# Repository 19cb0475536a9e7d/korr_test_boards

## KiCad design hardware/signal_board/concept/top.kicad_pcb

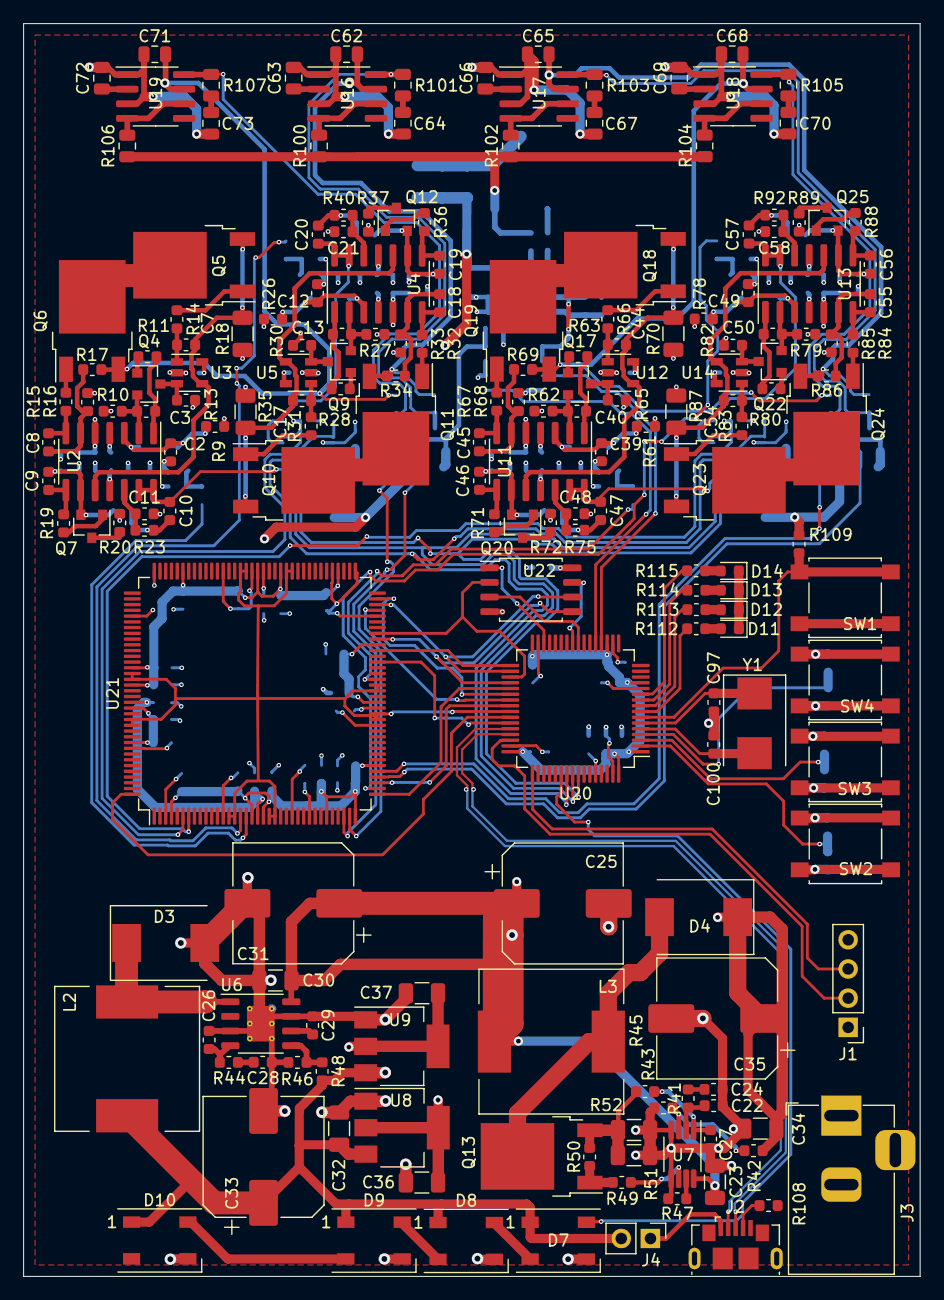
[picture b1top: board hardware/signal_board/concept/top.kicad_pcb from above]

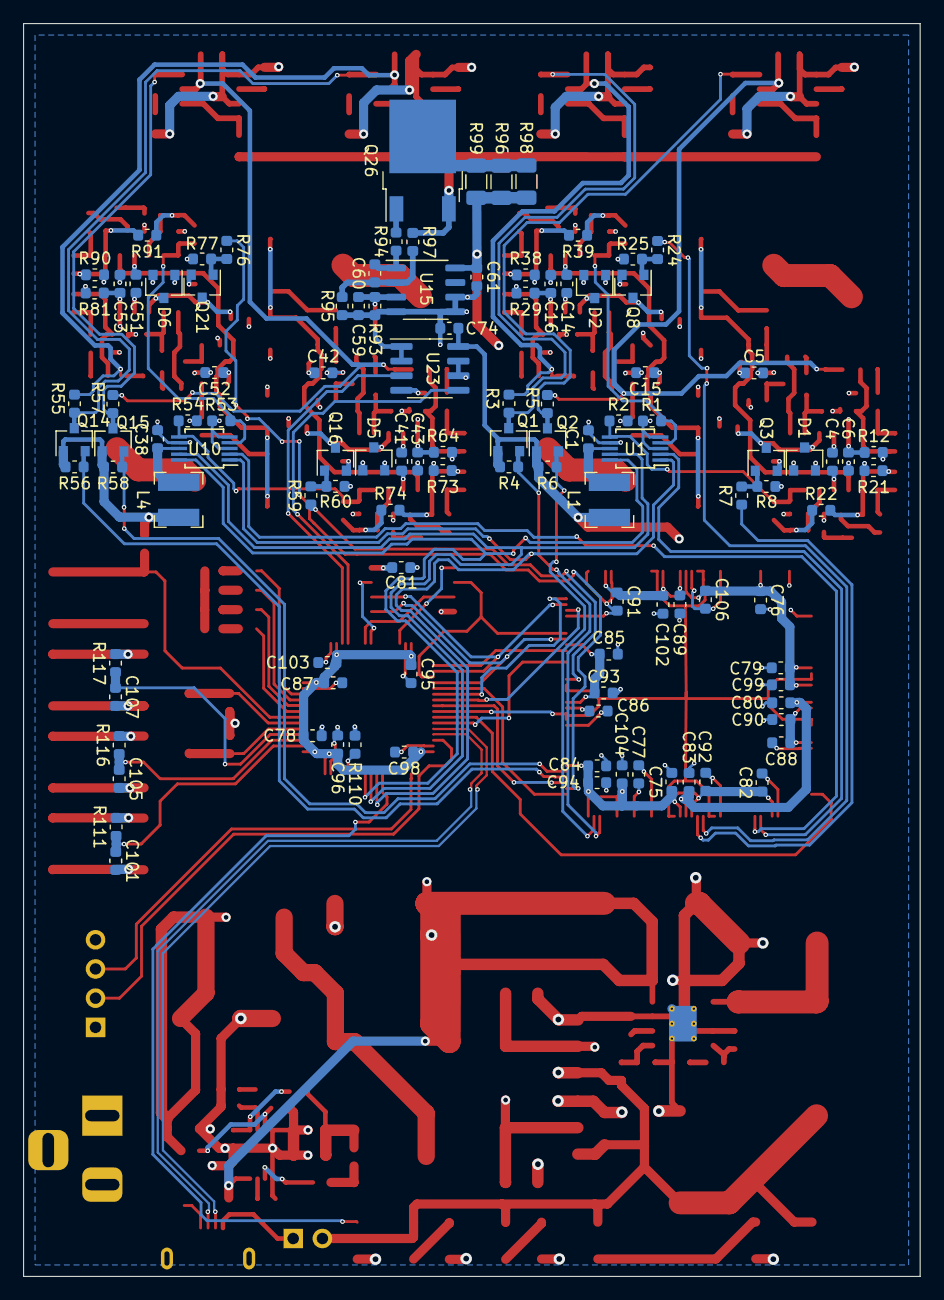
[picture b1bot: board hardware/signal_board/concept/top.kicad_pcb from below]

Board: 4 copper layers, 78.0 x 109.0 mm, 300 parts (111 on the bottom side), 186 nets.

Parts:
C1, C2, C4, C5, C6, C11, C12, C14, C15, C16, C21, C24, C27, C28, C29, C38, C39, C41, C42, C43, C48, C49, C51, C52, C53, C58, C59, C61, C74, C75, C76, C77, C78, C79, C80, C81, C82, C83, C84, C85, C86, C87, C88, C89, C90, C91, C92, C93, C94, C95, C96, C98, C99, C101, C102, C103, C104, C105, C106, C107: 0.1u; C_0603_1608Metric
C3, C7, C8, C9, C13, C17, C18, C19, C22, C26, C40, C44, C45, C46, C50, C54, C55, C56, C60: 100p; C_0603_1608Metric
C10, C20, C47, C57: 0.22u; C_0603_1608Metric
C23, C30, C32, C34, C36, C37: 1u; C_1206_3216Metric
C25, C31: 470u; CP_Elec_10x10
C33, C35: 100u; CP_Elec_10x10
C62, C65, C68, C71: 0.1u; C_0805_2012Metric
C63, C66, C69, C72: 470p; C_0805_2012Metric
C64, C67, C70, C73: 1u; C_0805_2012Metric
C97, C100: 10p; C_0603_1608Metric
D1, D2, D5, D6: BZX84Cxx; D_SOT-23_ANK
D3, D4: D_Schottky; D_SMC
D7, D8, D9, D10: WS2812B; LED_WS2812B_PLCC4_5.0x5.0mm_P3.2mm
D11, D12, D13, D14: LED; LED_0603_1608Metric
J1: Conn_01x04; PinHeader_1x04_P2.54mm_Vertical
J2: USB_OTG; USB_Micro-B_GCT_USB3076-30-A
J3: Barrel_Jack_Switch; BarrelJack_Horizontal
J4: Conn_01x02; PinHeader_1x02_P2.54mm_Vertical
L1, L4: 10u; L_Bourns-SRN4018
L2, L3: 10u; L_12x12mm_H8mm
Q1, Q2, Q3, Q4, Q7, Q8, Q9, Q12, Q14, Q15, Q16, Q17, Q20, Q21, Q22, Q25: Q_NMOS_GSD; SOT-23
Q5, Q10, Q18, Q23: Q_PMOS_GDS; TO-252-2
Q6, Q11, Q13, Q19, Q24, Q26: Q_NMOS_GDS; TO-252-2
R1, R2, R3, R4, R5, R6, R8, R9, R10, R13, R20, R21, R25, R26, R27, R30, R37, R38, R53, R54, R55, R56, R57, R58, R60, R61, R62, R65, R72, R73, R77, R78, R79, R82, R89, R90, R109, R110: 10k; R_0603_1608Metric
R7, R24, R59, R76: 100; R_0603_1608Metric
R11, R14, R15, R16, R19, R22, R23, R28, R31, R32, R33, R36, R39, R40, R41, R44, R63, R66, R67, R68, R71, R74, R75, R80, R83, R84, R85, R88, R91, R92, R94, R95, R97, R108, R111, R112, R113, R114, R115, R116, R117: 1k; R_0603_1608Metric
R12, R29, R64, R81, R93: 100k; R_0603_1608Metric
R17, R34, R69, R86: 9.1k; R_0603_1608Metric
R18, R35, R70, R87: 1k; R_1206_3216Metric
R42, R43, R45, R46, R47, R48, R50: 10K; R_0603_1608Metric
R49: 22; R_0603_1608Metric
R51, R52: 0.1; R_1206_3216Metric
R96, R98, R99: 100; R_1206_3216Metric
R100, R102, R104, R106: 470; R_0805_2012Metric
R101, R103, R105, R107: 10k; R_0805_2012Metric
SW1, SW2, SW3, SW4: SW_Push; SW_SPST_B3S-1000
U1, U10: ADS1118IDGS; MSOP-10_3x3mm_P0.5mm
U2, U4, U11, U13: LM324; SOIC-14_3.9x8.7mm_P1.27mm
U3, U5, U12, U14: MCP6001-OT; SOT-23-5
U6: L5973D; HSOP-8-1EP_3.9x4.9mm_P1.27mm_EP2.41x3.1mm_ThermalVias
U7: LM3488MM; MSOP-8_3x3mm_P0.65mm
U8: AMS1117-3.3; SOT-223-3_TabPin2
U9: AMS1117; SOT-223-3_TabPin2
U15: LM358; SO-8_3.9x4.9mm_P1.27mm
U16, U17, U18, U19: IR1155S; SOIC-8_3.9x4.9mm_P1.27mm
U20: STM32F103R(F-G)Tx_u; LQFP-64_10x10mm_P0.5mm
U21: XC6SLX9-TQG144; TQFP-144_20x20mm_P0.5mm
U22: W25Q32JVSS; SOIC-8_5.23x5.23mm_P1.27mm
U23: MCP6002-xMS; SOIC-8_3.9x4.9mm_P1.27mm
Y1: 8MHz; Crystal_SMD_7050-2Pin_7.0x5.0mm

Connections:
/ADS1118_MISO: U1.9, U10.9, U20.56
/ADS1118_MOSI: U1.10, U10.10, U20.57
/ADS1118_NCS_0: U1.2, U21.6
/ADS1118_NCS_1: U10.2, U21.7
/ADS1118_SCK: U1.1, U10.1, U20.55
/Cell_0_Sheet/CurrentSource_A_Sheet/PFC_CRNT: C20.1, R1.1, U1.4, U4.13, U4.14
/Cell_0_Sheet/CurrentSource_B_Sheet/PFC_CRNT: C10.1, R2.1, U1.6, U2.13, U2.14
/Cell_1_Sheet/CurrentSource_A_Sheet/PFC_CRNT: C57.1, R53.1, U10.4, U13.13, U13.14
/Cell_1_Sheet/CurrentSource_B_Sheet/PFC_CRNT: C47.1, R54.1, U10.6, U11.13, U11.14
/CoreSheet/STM32F103_BTN_0: C101.1, R111.1, U20.2
/CoreSheet/STM32F103_BTN_1: C105.1, R116.1, U20.3
/CoreSheet/STM32F103_BTN_2: C107.1, R117.1, U20.4
/CoreSheet/STM32F103_SIG_LED_0: R112.1, U20.8
/CoreSheet/STM32F103_SIG_LED_1: R113.1, U20.9
/CoreSheet/STM32F103_SIG_LED_2: R114.1, U20.10
/CoreSheet/STM32F103_SIG_LED_3: R115.1, U20.11
/CoreSheet/U_PFC_FB_OVP_ADJ_DAC: U20.20, U23.3
/CoreSheet/U_PFC_VCC_ADJ_DAC: U20.21, U23.5
/CoreSheet/W25Q32_HOLD: U20.25, U22.7
/CoreSheet/W25Q32_NCS: U20.30, U22.1
/CoreSheet/W25Q32_NWP: U20.24, U22.3
/CoreSheet/XC6SLX9_CLK: U20.41, U21.14, U21.15, U21.21, U21.22, U21.50, U21.51, U21.55, U21.56, U21.84, U21.85, U21.92, U21.93, U21.123, U21.124, U21.131, U21.132
/CoreSheet/XC6SLX9_DONE: U20.38, U21.71
/CoreSheet/XC6SLX9_HSWAPEN: U20.42, U21.144
/CoreSheet/XC6SLX9_INIT_B: U20.40, U21.39
/CoreSheet/XC6SLX9_M0: U20.39, U21.69
/CoreSheet/XC6SLX9_M1: U20.43, U21.60
/CoreSheet/XC6SLX9_NCS: U20.33, U21.62
/CoreSheet/XC6SLX9_PRG_B: U20.37, U21.37
/CoreSheet/XC6SLX9_W25Q32_MISO: U20.35, U21.65, U22.2
/CoreSheet/XC6SLX9_W25Q32_MOSI: U20.36, U21.64, U22.5
/CoreSheet/XC6SLX9_W25Q32_SCK: U20.34, U21.70, U22.6
/PFC_DUT_FB_OVP: Q26.3, R97.1, R100.1, R102.1, R104.1, R106.1
/PFC_GATE_HIGH_0: Q1.3, R3.1, R101.1, U16.8
/PFC_GATE_HIGH_1: Q2.3, R5.1, R107.1, U19.8
/PFC_GATE_HIGH_2: Q14.3, R55.1, R103.1, U17.8
/PFC_GATE_HIGH_3: Q15.3, R57.1, R105.1, U18.8
/PFC_GATE_LOW_0: Q1.2, R4.1, U21.34
/PFC_GATE_LOW_1: Q2.2, R6.1, U21.35
/PFC_GATE_LOW_2: Q14.2, R56.1, U21.40
/PFC_GATE_LOW_3: Q15.2, R58.1, U21.41
/PFC_STOP_0: R24.1, U21.16
/PFC_STOP_1: R7.1, U21.17
/PFC_STOP_2: R76.1, U21.38
/PFC_STOP_3: R59.1, U21.57
/PFC_VCC_DUT_0: C62.1, Q11.3, R3.2, R34.1, U16.7
/PFC_VCC_DUT_1: C71.1, Q6.3, R5.2, R17.1, U19.7
/PFC_VCC_DUT_2: C65.1, Q24.3, R55.2, R86.1, U17.7
/PFC_VCC_DUT_3: C68.1, Q19.3, R57.2, R69.1, U18.7
/STM32F103_SWCLK: J1.2, U20.46
/STM32F103_SWDIO: J1.3, U20.49
/STM32F103_USB_D+: J2.3, U20.45
/STM32F103_USB_D-: J2.2, U20.44
/U_PFC_FB_OVP_ADJ: C59.1, R93.1, U15.3, U23.1, U23.2
/U_PFC_VCC_ADJ: C6.1, C16.1, C43.1, C53.1, R12.1, R29.1, R64.1, R81.1, U2.5, U4.5, U11.5, U13.5, U23.6, U23.7
/VCC5V: C5.1, C15.1, C32.1, C33.1, C42.1, C52.1, D7.1, D8.1, D9.1, D10.1, J4.2, L2.2, R9.2, R26.2, R48.2, R61.2, R78.2, U3.5, U5.5, U8.3, U9.3, U12.5, U14.5
/VCC12V: C23.1, C25.1, C30.1, C31.1, C61.1, J3.1, L3.1, R96.1, R98.1, R99.1, U6.8, U7.8, U15.8
/VCC30V: C4.1, C14.1, C34.1, C35.1, C41.1, C51.1, D4.1, R13.1, R18.1, R20.1, R30.1, R35.1, R37.1, R42.2, R65.1, R70.1, R72.1, R82.1, R87.1, R89.1, U2.4, U4.4, U11.4, U13.4
/VDD1.25V: C37.2, C77.1, C80.1, C83.1, C86.1, C89.1, U9.2, U21.19, U21.28, U21.52, U21.89, U21.128
/VDD3.3V: C36.1, C74.1, C75.1, C76.1, C78.1, C79.1, C81.1, C82.1, C84.1, C85.1, C87.1, C88.1, C90.1, C91.1, C92.1, C93.1, C94.1, C95.1, C96.1, C98.1, C99.1, C102.1, C103.1, C104.1, C106.1, J1.4, L1.2, L4.2, Q1.1, Q2.1, Q14.1, Q15.1, R4.2, R6.2, R56.2, R58.2, R109.1, U8.2, U20.1, U20.13, U20.19, U20.32, U20.48, U20.64, U21.4, U21.18, U21.20, U21.31, U21.36, U21.42, U21.53, U21.63, U21.76, U21.86, U21.90, U21.103, U21.122, U21.125, U21.129, U21.135, U22.8, U23.8
/WS2812B_DIN: D7.4, U20.54
GNDA: C1.2, C2.2, C4.2, C5.2, C6.2, C11.2, C12.2, C14.2, C15.2, C16.2, C21.2, C22.2, C23.2, C24.2, C25.2, C26.2, C27.2, C28.2, C29.2, C30.2, C31.2, C32.2, C33.2, C34.2, C35.2, C36.2, C37.1, C38.2, C39.2, C41.2, C42.2, C43.2, C48.2, C49.2, C51.2, C52.2, C53.2, C58.2, C59.2, C61.2, C62.2, C63.2, C64.2, C65.2, C66.2, C67.2, C68.2, C69.2, C70.2, C71.2, C72.2, C73.2, C74.2, C75.2, C76.2, C77.2, C78.2, C79.2, C80.2, C81.2, C82.2, C83.2, C84.2, C85.2, C86.2, C87.2, C88.2, C89.2, C90.2, C91.2, C92.2, C93.2, C94.2, C95.2, C96.2, C97.2, C98.2, C99.2, C100.2, C101.2, C102.2, C103.2, C104.2, C105.2, C106.2, C107.2, D1.2, D2.2, D3.2, D5.2, D6.2, D7.3, D8.3, D9.3, D10.3, D11.1, D12.1, D13.1, D14.1, J1.1, J2.5, J2.6, J3.2, J3.3, Q3.2, Q8.2, Q16.2, Q21.2, R1.2, R2.2, R8.2, R10.2, R12.2, R16.2, R21.2, R25.2, R27.2, R29.2, R33.2, R38.2, R43.1, R46.1, R47.1, R51.1, R52.1, R53.2, R54.2, R60.2, R62.2, R64.2, R68.2, R73.2, R77.2, R79.2, R81.2, R85.2, R90.2, R93.2, R95.2, R108.2, R110.2, SW1.2, SW2.2, SW3.2, SW4.2, U1.3, U1.5, U1.7, U2.11, U3.2, U4.11, U5.2, U6.3, U6.7, U6.9, U7.4, U7.5, U8.1, U9.1, U10.3, U10.5, U10.7, U11.11, U12.2, U13.11, U14.2, U15.4, U15.5, U15.6, U16.1, U16.3, U17.1, U17.3, U18.1, U18.3, U19.1, U19.3, U20.12, U20.18, U20.31, U20.47, U20.63, U21.3, U21.13, U21.25, U21.49, U21.54, U21.68, U21.73, U21.77, U21.91, U21.96, U21.108, U21.113, U21.130, U21.136, U22.4, U23.4
unnamed: C1.1, L1.1, U1.8
unnamed: C2.1, D1.1, Q3.3, R9.1, U2.3
unnamed: C3.1, R11.2, U2.1
unnamed: C3.2, Q4.2, R10.1, U2.2
unnamed: C7.1, R14.2, U3.1
unnamed: C7.2, Q5.3, R18.2, U2.10, U3.4
unnamed: C8.1, R15.2, U2.7
unnamed: C8.2, R16.1, R17.2, U2.6
unnamed: C9.1, R19.2, U2.8
unnamed: C9.2, Q7.2, R21.1, R22.2, U2.9
unnamed: C10.2, R22.1, R23.2
unnamed: C11.1, R23.1, U2.12
unnamed: C12.1, D2.1, Q8.3, R26.1, U4.3
unnamed: C13.1, R28.2, U4.1
unnamed: C13.2, Q9.2, R27.1, U4.2
unnamed: C17.1, R31.2, U5.1
unnamed: C17.2, Q10.3, R35.2, U4.10, U5.4
unnamed: C18.1, R32.2, U4.7
unnamed: C18.2, R33.1, R34.2, U4.6
unnamed: C19.1, R36.2, U4.8
unnamed: C19.2, Q12.2, R38.1, R39.2, U4.9
unnamed: C20.2, R39.1, R40.2
unnamed: C21.1, R40.1, U4.12
unnamed: C22.1, R41.2, U7.2
unnamed: C24.1, R41.1
unnamed: C26.1, R44.2, U6.4
unnamed: C27.1, R45.1, U7.1
unnamed: C28.1, R44.1
unnamed: C29.1, U6.6
unnamed: C38.1, L4.1, U10.8
unnamed: C39.1, D5.1, Q16.3, R61.1, U11.3
unnamed: C40.1, R63.2, U11.1
unnamed: C40.2, Q17.2, R62.1, U11.2
unnamed: C44.1, R66.2, U12.1
unnamed: C44.2, Q18.3, R70.2, U11.10, U12.4
unnamed: C45.1, R67.2, U11.7
unnamed: C45.2, R68.1, R69.2, U11.6
unnamed: C46.1, R71.2, U11.8
unnamed: C46.2, Q20.2, R73.1, R74.2, U11.9
unnamed: C47.2, R74.1, R75.2
unnamed: C48.1, R75.1, U11.12
unnamed: C49.1, D6.1, Q21.3, R78.1, U13.3
unnamed: C50.1, R80.2, U13.1
unnamed: C50.2, Q22.2, R79.1, U13.2
unnamed: C54.1, R83.2, U14.1
unnamed: C54.2, Q23.3, R87.2, U13.10, U14.4
unnamed: C55.1, R84.2, U13.7
unnamed: C55.2, R85.1, R86.2, U13.6
unnamed: C56.1, R88.2, U13.8
unnamed: C56.2, Q25.2, R90.1, R91.2, U13.9
unnamed: C57.2, R91.1, R92.2
unnamed: C58.1, R92.1, U13.12
unnamed: C60.1, R94.2, U15.1
unnamed: C60.2, R95.1, R97.2, U15.2
unnamed: C63.1, U16.2
unnamed: C64.1, R101.2
unnamed: C66.1, U17.2
unnamed: C67.1, R103.2
unnamed: C69.1, U18.2
unnamed: C70.1, R105.2
unnamed: C72.1, U19.2
unnamed: C73.1, R107.2
unnamed: C97.1, U20.6, Y1.1
unnamed: C100.1, U20.5, Y1.2
unnamed: D3.1, L2.1, U6.1
unnamed: D4.2, L3.2, Q13.2
unnamed: D7.2, D8.4
unnamed: D8.2, D9.4
unnamed: D9.2, D10.4
unnamed: D11.2, R112.2
unnamed: D12.2, R113.2
unnamed: D13.2, R114.2
unnamed: D14.2, R115.2
unnamed: J2.1, J4.1
unnamed: J2.4, R108.1
unnamed: Q3.1, R7.2, R8.1
unnamed: Q4.1, R11.1
unnamed: Q4.3, R13.2, U3.3
unnamed: Q5.1, R14.1
unnamed: Q5.2, Q6.2
unnamed: Q6.1, R15.1
unnamed: Q7.1, R19.1
unnamed: Q7.3, R20.2
unnamed: Q8.1, R24.2, R25.1
unnamed: Q9.1, R28.1
unnamed: Q9.3, R30.2, U5.3
unnamed: Q10.1, R31.1
unnamed: Q10.2, Q11.2
unnamed: Q11.1, R32.1
unnamed: Q12.1, R36.1
unnamed: Q12.3, R37.2
unnamed: Q13.1, R49.2, R50.2
unnamed: Q13.3, R45.2, R50.1, R51.2, R52.2
unnamed: Q16.1, R59.2, R60.1
unnamed: Q17.1, R63.1
unnamed: Q17.3, R65.2, U12.3
unnamed: Q18.1, R66.1
unnamed: Q18.2, Q19.2
unnamed: Q19.1, R67.1
unnamed: Q20.1, R71.1
unnamed: Q20.3, R72.2
unnamed: Q21.1, R76.2, R77.1
unnamed: Q22.1, R80.1
unnamed: Q22.3, R82.2, U14.3
unnamed: Q23.1, R83.1
unnamed: Q23.2, Q24.2
unnamed: Q24.1, R84.1
unnamed: Q25.1, R88.1
unnamed: Q25.3, R89.2
unnamed: Q26.1, R94.1
unnamed: Q26.2, R96.2, R98.2, R99.2
unnamed: R42.1, R43.2, U7.3
unnamed: R46.2, R48.1, U6.5
unnamed: R47.2, U7.7
unnamed: R49.1, U7.6
unnamed: R100.2, U16.4, U16.6
unnamed: R102.2, U17.4, U17.6
unnamed: R104.2, U18.4, U18.6
unnamed: R106.2, U19.4, U19.6
unnamed: R109.2, SW1.1, U20.7
unnamed: R110.1, U20.60
unnamed: R111.2, SW2.1
unnamed: R116.2, SW3.1
unnamed: R117.2, SW4.1

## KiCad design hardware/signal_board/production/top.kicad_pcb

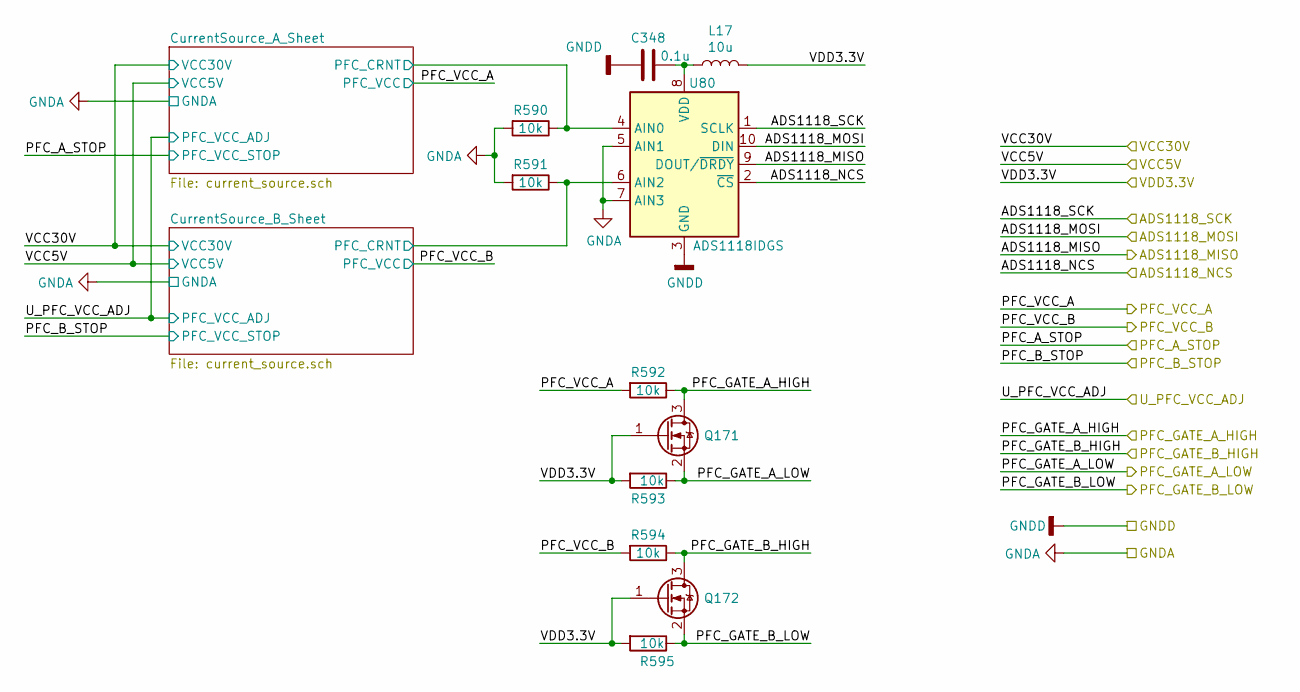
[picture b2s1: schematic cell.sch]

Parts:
C1: 0.1u; C_0603_1608Metric
L1: 10u; L_Bourns-SRN4018
Q1, Q2: Q_NMOS_GSD; SOT-23
R1, R2, R3, R4, R5, R6: 10k; R_0603_1608Metric
U1: ADS1118IDGS; MSOP-10_3x3mm_P0.5mm

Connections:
/ADS1118_MISO: U1.9 (DOUT/~DRDY); also elsewhere on the board
/ADS1118_MOSI: U1.10 (DIN); also elsewhere on the board
/ADS1118_NCS_0: U1.2 (~CS); also elsewhere on the board
/ADS1118_SCK: U1.1 (SCLK); also elsewhere on the board
/Cell_0_Sheet/CurrentSource_A_Sheet/PFC_CRNT: R1.1, U1.4 (AIN0); also elsewhere on the board
/Cell_0_Sheet/CurrentSource_B_Sheet/PFC_CRNT: R2.1, U1.6 (AIN2); also elsewhere on the board
/PFC_GATE_HIGH_0: Q1.3 (D), R3.1; also elsewhere on the board
/PFC_GATE_HIGH_1: Q2.3 (D), R5.1; also elsewhere on the board
/PFC_GATE_LOW_0: Q1.2 (S), R4.1; also elsewhere on the board
/PFC_GATE_LOW_1: Q2.2 (S), R6.1; also elsewhere on the board
/PFC_VCC_DUT_0: R3.2; also elsewhere on the board
/PFC_VCC_DUT_1: R5.2; also elsewhere on the board
/VDD3.3V: L1.2, Q1.1 (G), Q2.1 (G), R4.2, R6.2; also elsewhere on the board
GNDA: C1.2, R1.2, R2.2, U1.3 (GND), U1.5 (AIN1), U1.7 (AIN3); also elsewhere on the board
unnamed: C1.1, L1.1, U1.8 (VDD)

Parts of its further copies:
C38, C62, C117, C138, C159, C180, C201, C222, C243, C264, C285, C306, C327, C348: 0.1u; C_0603_1608Metric
L4, L5, L6, L7, L8, L9, L10, L11, L12, L13, L14, L15, L16, L17: 10u; L_Bourns-SRN4018
Q14, Q15, Q27, Q28, Q39, Q40, Q51, Q52, Q63, Q64, Q75, Q76, Q87, Q88, Q99, Q100, Q111, Q112, Q123, Q124, Q135, Q136, Q147, Q148, Q159, Q160, Q171, Q172: Q_NMOS_GSD; SOT-23
R53, R54, R55, R56, R57, R58, R100, R101, R102, R103, R104, R105, R150, R151, R152, R153, R154, R155, R190, R191, R192, R193, R194, R195, R230, R231, R232, R233, R234, R235, R270, R271, R272, R273, R274, R275, R310, R311, R312, R313, R314, R315, R350, R351, R352, R353, R354, R355, R390, R391, R392, R393, R394, R395, R430, R431, R432, R433, R434, R435, R470, R471, R472, R473, R474, R475, R510, R511, R512, R513, R514, R515, R550, R551, R552, R553, R554, R555, R590, R591, R592, R593, R594, R595: 10k; R_0603_1608Metric
U10, U16, U25, U30, U35, U40, U45, U50, U55, U60, U65, U70, U75, U80: ADS1118IDGS; MSOP-10_3x3mm_P0.5mm

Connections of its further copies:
/ADS1118_MISO: U10.9 (DOUT/~DRDY), U16.9 (DOUT/~DRDY), U25.9 (DOUT/~DRDY), U30.9 (DOUT/~DRDY), U35.9 (DOUT/~DRDY), U40.9 (DOUT/~DRDY), U45.9 (DOUT/~DRDY), U50.9 (DOUT/~DRDY), U55.9 (DOUT/~DRDY), U60.9 (DOUT/~DRDY), U65.9 (DOUT/~DRDY), U70.9 (DOUT/~DRDY), U75.9 (DOUT/~DRDY), U80.9 (DOUT/~DRDY); also elsewhere on the board
/ADS1118_MOSI: U10.10 (DIN), U16.10 (DIN), U25.10 (DIN), U30.10 (DIN), U35.10 (DIN), U40.10 (DIN), U45.10 (DIN), U50.10 (DIN), U55.10 (DIN), U60.10 (DIN), U65.10 (DIN), U70.10 (DIN), U75.10 (DIN), U80.10 (DIN); also elsewhere on the board
/ADS1118_NCS_1: U10.2 (~CS); also elsewhere on the board
/ADS1118_NCS_2: U16.2 (~CS); also elsewhere on the board
/ADS1118_NCS_3: U25.2 (~CS); also elsewhere on the board
/ADS1118_NCS_4: U30.2 (~CS); also elsewhere on the board
/ADS1118_NCS_5: U35.2 (~CS); also elsewhere on the board
/ADS1118_NCS_6: U40.2 (~CS); also elsewhere on the board
/ADS1118_NCS_7: U45.2 (~CS); also elsewhere on the board
/ADS1118_NCS_8: U50.2 (~CS); also elsewhere on the board
/ADS1118_NCS_9: U55.2 (~CS); also elsewhere on the board
/ADS1118_NCS_10: U60.2 (~CS); also elsewhere on the board
/ADS1118_NCS_11: U65.2 (~CS); also elsewhere on the board
/ADS1118_NCS_12: U70.2 (~CS); also elsewhere on the board
/ADS1118_NCS_13: U75.2 (~CS); also elsewhere on the board
/ADS1118_NCS_14: U80.2 (~CS); also elsewhere on the board
/ADS1118_SCK: U10.1 (SCLK), U16.1 (SCLK), U25.1 (SCLK), U30.1 (SCLK), U35.1 (SCLK), U40.1 (SCLK), U45.1 (SCLK), U50.1 (SCLK), U55.1 (SCLK), U60.1 (SCLK), U65.1 (SCLK), U70.1 (SCLK), U75.1 (SCLK), U80.1 (SCLK); also elsewhere on the board
/Cell_1_Sheet/CurrentSource_A_Sheet/PFC_CRNT: R53.1, U10.4 (AIN0); also elsewhere on the board
/Cell_1_Sheet/CurrentSource_B_Sheet/PFC_CRNT: R54.1, U10.6 (AIN2); also elsewhere on the board
/Cell_2_Sheet/CurrentSource_A_Sheet/PFC_CRNT: R100.1, U16.4 (AIN0); also elsewhere on the board
/Cell_2_Sheet/CurrentSource_B_Sheet/PFC_CRNT: R101.1, U16.6 (AIN2); also elsewhere on the board
/Cell_3_Sheet/CurrentSource_A_Sheet/PFC_CRNT: R150.1, U25.4 (AIN0); also elsewhere on the board
/Cell_3_Sheet/CurrentSource_B_Sheet/PFC_CRNT: R151.1, U25.6 (AIN2); also elsewhere on the board
/PFC_GATE_HIGH_2: Q14.3 (D), R55.1; also elsewhere on the board
/PFC_GATE_HIGH_3: Q15.3 (D), R57.1; also elsewhere on the board
/PFC_GATE_HIGH_4: Q27.3 (D), R102.1; also elsewhere on the board
/PFC_GATE_HIGH_5: Q28.3 (D), R104.1; also elsewhere on the board
/PFC_GATE_HIGH_6: Q39.3 (D), R152.1; also elsewhere on the board
/PFC_GATE_HIGH_7: Q40.3 (D), R154.1; also elsewhere on the board
/PFC_GATE_HIGH_8: Q51.3 (D), R192.1; also elsewhere on the board
/PFC_GATE_HIGH_9: Q52.3 (D), R194.1; also elsewhere on the board
/PFC_GATE_HIGH_10: Q63.3 (D), R232.1; also elsewhere on the board
/PFC_GATE_HIGH_11: Q64.3 (D), R234.1; also elsewhere on the board
/PFC_GATE_HIGH_12: Q75.3 (D), R272.1; also elsewhere on the board
/PFC_GATE_HIGH_13: Q76.3 (D), R274.1; also elsewhere on the board
/PFC_GATE_HIGH_14: Q87.3 (D), R312.1; also elsewhere on the board
/PFC_GATE_HIGH_15: Q88.3 (D), R314.1; also elsewhere on the board
/PFC_GATE_HIGH_16: Q99.3 (D), R352.1; also elsewhere on the board
/PFC_GATE_HIGH_17: Q100.3 (D), R354.1; also elsewhere on the board
/PFC_GATE_HIGH_18: Q111.3 (D), R392.1; also elsewhere on the board
/PFC_GATE_HIGH_19: Q112.3 (D), R394.1; also elsewhere on the board
/PFC_GATE_HIGH_20: Q123.3 (D), R432.1; also elsewhere on the board
/PFC_GATE_HIGH_21: Q124.3 (D), R434.1; also elsewhere on the board
/PFC_GATE_HIGH_22: Q135.3 (D), R472.1; also elsewhere on the board
/PFC_GATE_HIGH_23: Q136.3 (D), R474.1; also elsewhere on the board
/PFC_GATE_HIGH_24: Q147.3 (D), R512.1; also elsewhere on the board
/PFC_GATE_HIGH_25: Q148.3 (D), R514.1; also elsewhere on the board
/PFC_GATE_HIGH_26: Q159.3 (D), R552.1; also elsewhere on the board
/PFC_GATE_HIGH_27: Q160.3 (D), R554.1; also elsewhere on the board
/PFC_GATE_HIGH_28: Q171.3 (D), R592.1; also elsewhere on the board
/PFC_GATE_HIGH_29: Q172.3 (D), R594.1; also elsewhere on the board
/PFC_GATE_LOW_2: Q14.2 (S), R56.1; also elsewhere on the board
/PFC_GATE_LOW_3: Q15.2 (S), R58.1; also elsewhere on the board
/PFC_GATE_LOW_4: Q27.2 (S), R103.1; also elsewhere on the board
/PFC_GATE_LOW_5: Q28.2 (S), R105.1; also elsewhere on the board
/PFC_GATE_LOW_6: Q39.2 (S), R153.1; also elsewhere on the board
/PFC_GATE_LOW_7: Q40.2 (S), R155.1; also elsewhere on the board
/PFC_GATE_LOW_8: Q51.2 (S), R193.1; also elsewhere on the board
/PFC_GATE_LOW_9: Q52.2 (S), R195.1; also elsewhere on the board
/PFC_GATE_LOW_10: Q63.2 (S), R233.1; also elsewhere on the board
/PFC_GATE_LOW_11: Q64.2 (S), R235.1; also elsewhere on the board
/PFC_GATE_LOW_12: Q75.2 (S), R273.1; also elsewhere on the board
/PFC_GATE_LOW_13: Q76.2 (S), R275.1; also elsewhere on the board
/PFC_GATE_LOW_14: Q87.2 (S), R313.1; also elsewhere on the board
/PFC_GATE_LOW_15: Q88.2 (S), R315.1; also elsewhere on the board
/PFC_GATE_LOW_16: Q99.2 (S), R353.1; also elsewhere on the board
/PFC_GATE_LOW_17: Q100.2 (S), R355.1; also elsewhere on the board
/PFC_GATE_LOW_18: Q111.2 (S), R393.1; also elsewhere on the board
/PFC_GATE_LOW_19: Q112.2 (S), R395.1; also elsewhere on the board
/PFC_GATE_LOW_20: Q123.2 (S), R433.1; also elsewhere on the board
/PFC_GATE_LOW_21: Q124.2 (S), R435.1; also elsewhere on the board
/PFC_GATE_LOW_22: Q135.2 (S), R473.1; also elsewhere on the board
/PFC_GATE_LOW_23: Q136.2 (S), R475.1; also elsewhere on the board
/PFC_GATE_LOW_24: Q147.2 (S), R513.1; also elsewhere on the board
/PFC_GATE_LOW_25: Q148.2 (S), R515.1; also elsewhere on the board
/PFC_GATE_LOW_26: Q159.2 (S), R553.1; also elsewhere on the board
/PFC_GATE_LOW_27: Q160.2 (S), R555.1; also elsewhere on the board
/PFC_GATE_LOW_28: Q171.2 (S), R593.1; also elsewhere on the board
/PFC_GATE_LOW_29: Q172.2 (S), R595.1; also elsewhere on the board
/PFC_VCC_DUT_2: R55.2; also elsewhere on the board
/PFC_VCC_DUT_3: R57.2; also elsewhere on the board
/PFC_VCC_DUT_4: R102.2; also elsewhere on the board
/PFC_VCC_DUT_5: R104.2; also elsewhere on the board
/PFC_VCC_DUT_6: R152.2; also elsewhere on the board
/PFC_VCC_DUT_7: R154.2; also elsewhere on the board
/PFC_VCC_DUT_8: R192.2; also elsewhere on the board
/PFC_VCC_DUT_9: R194.2; also elsewhere on the board
/PFC_VCC_DUT_10: R232.2; also elsewhere on the board
/PFC_VCC_DUT_11: R234.2; also elsewhere on the board
/PFC_VCC_DUT_12: R272.2; also elsewhere on the board
/PFC_VCC_DUT_13: R274.2; also elsewhere on the board
/PFC_VCC_DUT_14: R312.2; also elsewhere on the board
/PFC_VCC_DUT_15: R314.2; also elsewhere on the board
/PFC_VCC_DUT_16: R352.2; also elsewhere on the board
/PFC_VCC_DUT_17: R354.2; also elsewhere on the board
/PFC_VCC_DUT_18: R392.2; also elsewhere on the board
/PFC_VCC_DUT_19: R394.2; also elsewhere on the board
/PFC_VCC_DUT_20: R432.2; also elsewhere on the board
/PFC_VCC_DUT_21: R434.2; also elsewhere on the board
/PFC_VCC_DUT_22: R472.2; also elsewhere on the board
/PFC_VCC_DUT_23: R474.2; also elsewhere on the board
/PFC_VCC_DUT_24: R512.2; also elsewhere on the board
/PFC_VCC_DUT_25: R514.2; also elsewhere on the board
/PFC_VCC_DUT_26: R552.2; also elsewhere on the board
/PFC_VCC_DUT_27: R554.2; also elsewhere on the board
/PFC_VCC_DUT_28: R592.2; also elsewhere on the board
/PFC_VCC_DUT_29: R594.2; also elsewhere on the board
/VDD3.3V: L4.2, L5.2, L6.2, L7.2, L8.2, L9.2, L10.2, L11.2, L12.2, L13.2, L14.2, L15.2, L16.2, L17.2, Q14.1 (G), Q15.1 (G), Q27.1 (G), Q28.1 (G), Q39.1 (G), Q40.1 (G), Q51.1 (G), Q52.1 (G), Q63.1 (G), Q64.1 (G), Q75.1 (G), Q76.1 (G), Q87.1 (G), Q88.1 (G), Q99.1 (G), Q100.1 (G), Q111.1 (G), Q112.1 (G), Q123.1 (G), Q124.1 (G), Q135.1 (G), Q136.1 (G), Q147.1 (G), Q148.1 (G), Q159.1 (G), Q160.1 (G), Q171.1 (G), Q172.1 (G), R56.2, R58.2, R103.2, R105.2, R153.2, R155.2, R193.2, R195.2, R233.2, R235.2, R273.2, R275.2, R313.2, R315.2, R353.2, R355.2, R393.2, R395.2, R433.2, R435.2, R473.2, R475.2, R513.2, R515.2, R553.2, R555.2, R593.2, R595.2; also elsewhere on the board
/sheet5E9AFF1E/CurrentSource_A_Sheet/PFC_CRNT: R430.1, U60.4 (AIN0); also elsewhere on the board
/sheet5E9AFF1E/CurrentSource_B_Sheet/PFC_CRNT: R431.1, U60.6 (AIN2); also elsewhere on the board
/sheet5E9AFF1F/CurrentSource_A_Sheet/PFC_CRNT: R470.1, U65.4 (AIN0); also elsewhere on the board
/sheet5E9AFF1F/CurrentSource_B_Sheet/PFC_CRNT: R471.1, U65.6 (AIN2); also elsewhere on the board
/sheet5E9AFF20/CurrentSource_A_Sheet/PFC_CRNT: R510.1, U70.4 (AIN0); also elsewhere on the board
/sheet5E9AFF20/CurrentSource_B_Sheet/PFC_CRNT: R511.1, U70.6 (AIN2); also elsewhere on the board
/sheet5E9AFF21/CurrentSource_A_Sheet/PFC_CRNT: R550.1, U75.4 (AIN0); also elsewhere on the board
/sheet5E9AFF21/CurrentSource_B_Sheet/PFC_CRNT: R551.1, U75.6 (AIN2); also elsewhere on the board
/sheet5E9AFF22/CurrentSource_A_Sheet/PFC_CRNT: R590.1, U80.4 (AIN0); also elsewhere on the board
/sheet5E9AFF22/CurrentSource_B_Sheet/PFC_CRNT: R591.1, U80.6 (AIN2); also elsewhere on the board
/sheet5E8790F9/CurrentSource_A_Sheet/PFC_CRNT: R190.1, U30.4 (AIN0); also elsewhere on the board
/sheet5E8790F9/CurrentSource_B_Sheet/PFC_CRNT: R191.1, U30.6 (AIN2); also elsewhere on the board
/sheet5E9528FB/CurrentSource_A_Sheet/PFC_CRNT: R230.1, U35.4 (AIN0); also elsewhere on the board
/sheet5E9528FB/CurrentSource_B_Sheet/PFC_CRNT: R231.1, U35.6 (AIN2); also elsewhere on the board
/sheet5E9528FC/CurrentSource_A_Sheet/PFC_CRNT: R270.1, U40.4 (AIN0); also elsewhere on the board
/sheet5E9528FC/CurrentSource_B_Sheet/PFC_CRNT: R271.1, U40.6 (AIN2); also elsewhere on the board
/sheet5E9528FD/CurrentSource_A_Sheet/PFC_CRNT: R310.1, U45.4 (AIN0); also elsewhere on the board
/sheet5E9528FD/CurrentSource_B_Sheet/PFC_CRNT: R311.1, U45.6 (AIN2); also elsewhere on the board
/sheet5E9528FE/CurrentSource_A_Sheet/PFC_CRNT: R350.1, U50.4 (AIN0); also elsewhere on the board
/sheet5E9528FE/CurrentSource_B_Sheet/PFC_CRNT: R351.1, U50.6 (AIN2); also elsewhere on the board
/sheet5E9528FF/CurrentSource_A_Sheet/PFC_CRNT: R390.1, U55.4 (AIN0); also elsewhere on the board
/sheet5E9528FF/CurrentSource_B_Sheet/PFC_CRNT: R391.1, U55.6 (AIN2); also elsewhere on the board
GNDA: C38.2, C62.2, C117.2, C138.2, C159.2, C180.2, C201.2, C222.2, C243.2, C264.2, C285.2, C306.2, C327.2, C348.2, R53.2, R54.2, R100.2, R101.2, R150.2, R151.2, R190.2, R191.2, R230.2, R231.2, R270.2, R271.2, R310.2, R311.2, R350.2, R351.2, R390.2, R391.2, R430.2, R431.2, R470.2, R471.2, R510.2, R511.2, R550.2, R551.2, R590.2, R591.2, U10.3 (GND), U10.5 (AIN1), U10.7 (AIN3), U16.3 (GND), U16.5 (AIN1), U16.7 (AIN3), U25.3 (GND), U25.5 (AIN1), U25.7 (AIN3), U30.3 (GND), U30.5 (AIN1), U30.7 (AIN3), U35.3 (GND), U35.5 (AIN1), U35.7 (AIN3), U40.3 (GND), U40.5 (AIN1), U40.7 (AIN3), U45.3 (GND), U45.5 (AIN1), U45.7 (AIN3), U50.3 (GND), U50.5 (AIN1), U50.7 (AIN3), U55.3 (GND), U55.5 (AIN1), U55.7 (AIN3), U60.3 (GND), U60.5 (AIN1), U60.7 (AIN3), U65.3 (GND), U65.5 (AIN1), U65.7 (AIN3), U70.3 (GND), U70.5 (AIN1), U70.7 (AIN3), U75.3 (GND), U75.5 (AIN1), U75.7 (AIN3), U80.3 (GND), U80.5 (AIN1), U80.7 (AIN3); also elsewhere on the board
unnamed: C38.1, L4.1, U10.8 (VDD)
unnamed: C62.1, L5.1, U16.8 (VDD)
unnamed: C117.1, L6.1, U25.8 (VDD)
unnamed: C138.1, L7.1, U30.8 (VDD)
unnamed: C159.1, L8.1, U35.8 (VDD)
unnamed: C180.1, L9.1, U40.8 (VDD)
unnamed: C201.1, L10.1, U45.8 (VDD)
unnamed: C222.1, L11.1, U50.8 (VDD)
unnamed: C243.1, L12.1, U55.8 (VDD)
unnamed: C264.1, L13.1, U60.8 (VDD)
unnamed: C285.1, L14.1, U65.8 (VDD)
unnamed: C306.1, L15.1, U70.8 (VDD)
unnamed: C327.1, L16.1, U75.8 (VDD)
unnamed: C348.1, L17.1, U80.8 (VDD)

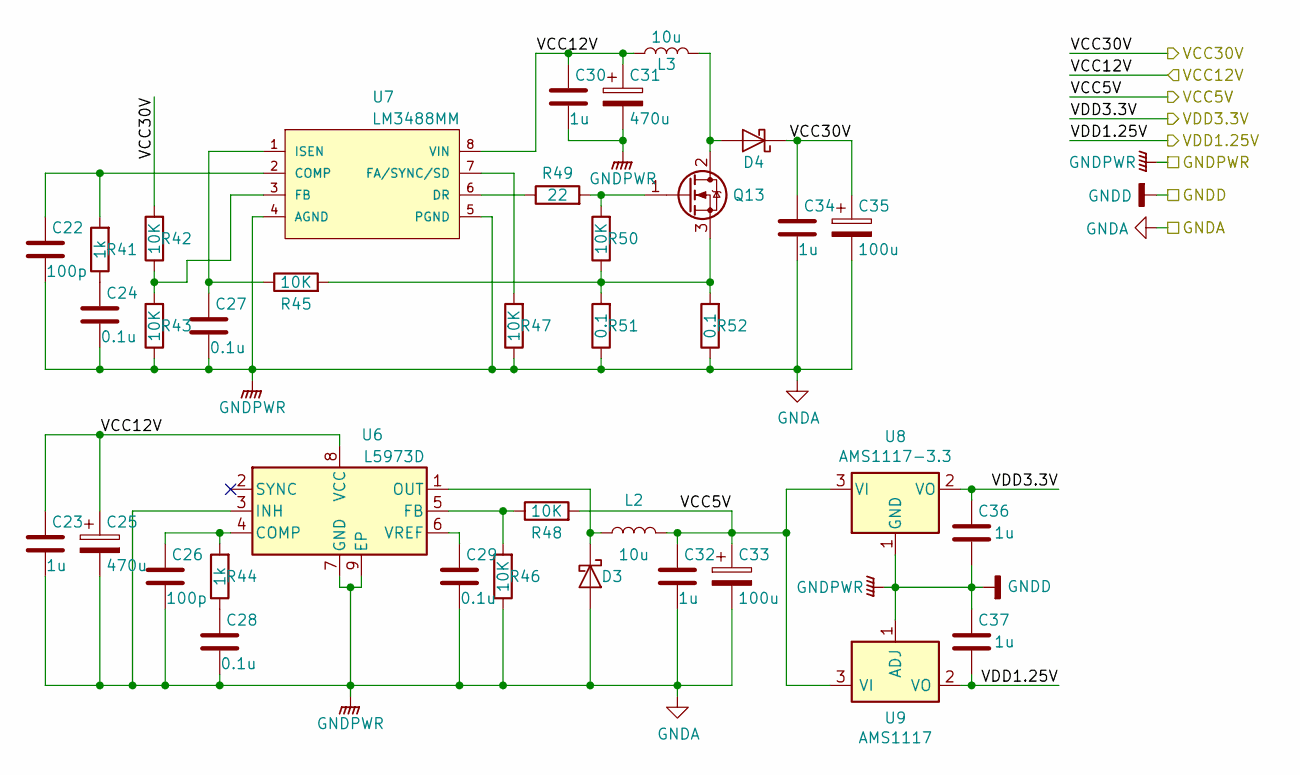
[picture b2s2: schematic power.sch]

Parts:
C22, C26: 100p; C_0603_1608Metric
C23, C30, C32, C34, C36, C37: 1u; C_1206_3216Metric
C24, C27, C28, C29: 0.1u; C_0603_1608Metric
C25, C31: 470u; CP_Elec_10x10
C33, C35: 100u; CP_Elec_10x10
D3, D4: D_Schottky; D_SMC
L2, L3: 10u; L_12x12mm_H8mm
Q13: Q_NMOS_GDS; TO-252-2
R41, R44: 1k; R_0603_1608Metric
R42, R43, R45, R46, R47, R48, R50: 10K; R_0603_1608Metric
R49: 22; R_0603_1608Metric
R51, R52: 0.1; R_1206_3216Metric
U6: L5973D; HSOP-8-1EP_3.9x4.9mm_P1.27mm_EP2.41x3.1mm_ThermalVias
U7: LM3488MM; MSOP-8_3x3mm_P0.65mm
U8: AMS1117-3.3; SOT-223-3_TabPin2
U9: AMS1117; SOT-223-3_TabPin2

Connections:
/VCC5V: C32.1, C33.1, L2.2, R48.2, U8.3 (VI), U9.3 (VI); also elsewhere on the board
/VCC12V: C23.1, C25.1, C30.1, C31.1, L3.1, U6.8 (VCC), U7.8 (VIN); also elsewhere on the board
/VCC30V: C34.1, C35.1, D4.1 (K), R42.2; also elsewhere on the board
/VDD1.25V: C37.2, U9.2 (VO); also elsewhere on the board
/VDD3.3V: C36.1, U8.2 (VO); also elsewhere on the board
GNDA: C22.2, C23.2, C24.2, C25.2, C26.2, C27.2, C28.2, C29.2, C30.2, C31.2, C32.2, C33.2, C34.2, C35.2, C36.2, C37.1, D3.2 (A), R43.1, R46.1, R47.1, R51.1, R52.1, U6.3 (INH), U6.7 (GND), U6.9 (EP), U7.4 (AGND), U7.5 (PGND), U8.1 (GND), U9.1 (ADJ); also elsewhere on the board
unnamed: C22.1, R41.2, U7.2 (COMP)
unnamed: C24.1, R41.1
unnamed: C26.1, R44.2, U6.4 (COMP)
unnamed: C27.1, R45.1, U7.1 (ISEN)
unnamed: C28.1, R44.1
unnamed: C29.1, U6.6 (VREF)
unnamed: D3.1 (K), L2.1, U6.1 (OUT)
unnamed: D4.2 (A), L3.2, Q13.2 (D)
unnamed: Q13.1 (G), R49.2, R50.2
unnamed: Q13.3 (S), R45.2, R50.1, R51.2, R52.2
unnamed: R42.1, R43.2, U7.3 (FB)
unnamed: R46.2, R48.1, U6.5 (FB)
unnamed: R47.2, U7.7 (FA/SYNC/SD)
unnamed: R49.1, U7.6 (DR)

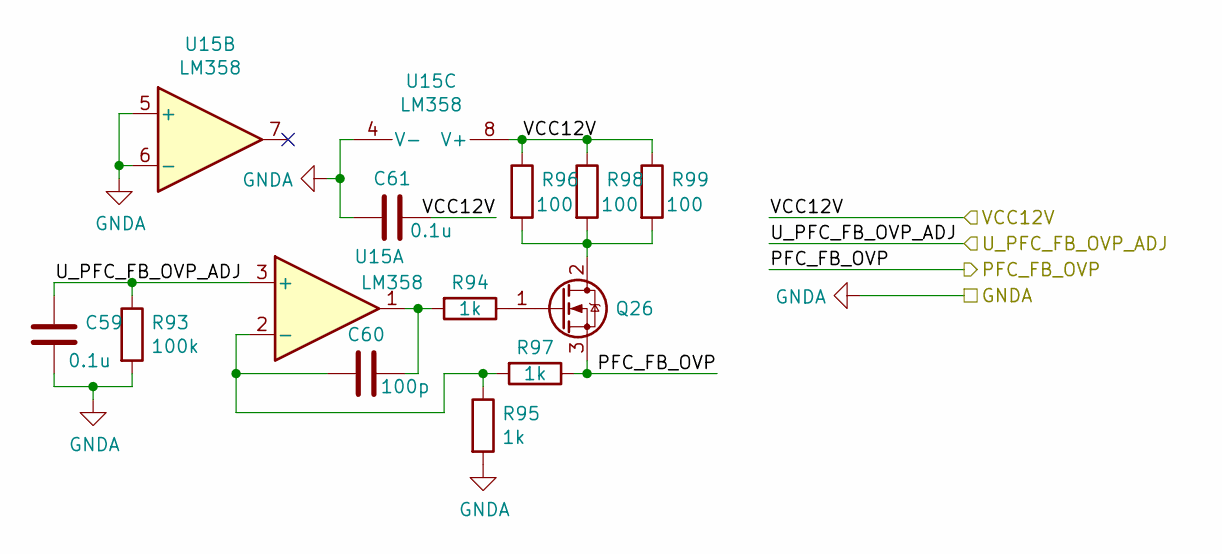
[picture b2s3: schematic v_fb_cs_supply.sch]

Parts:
C59, C61: 0.1u; C_0603_1608Metric
C60: 100p; C_0603_1608Metric
Q26: Q_NMOS_GDS; TO-252-2
R93: 100k; R_0603_1608Metric
R94, R95, R97: 1k; R_0603_1608Metric
R96, R98, R99: 100; R_1206_3216Metric
U15: LM358; SO-8_3.9x4.9mm_P1.27mm

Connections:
/PFC_DUT_FB_OVP: Q26.3 (S), R97.1
/U_PFC_FB_OVP_ADJ: C59.1, R93.1, U15.3 (+); also elsewhere on the board
/VCC12V: C61.1, R96.1, R98.1, R99.1, U15.8 (V+); also elsewhere on the board
GNDA: C59.2, C61.2, R93.2, R95.2, U15.4 (V-), U15.5 (+), U15.6 (-); also elsewhere on the board
unnamed: C60.1, R94.2, U15.1
unnamed: C60.2, R95.1, R97.2, U15.2 (-)
unnamed: Q26.1 (G), R94.1
unnamed: Q26.2 (D), R96.2, R98.2, R99.2
